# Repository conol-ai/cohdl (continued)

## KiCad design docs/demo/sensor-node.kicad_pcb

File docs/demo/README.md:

# MVP demo evidence

The acceptance test from the MVP Definition
(`docs/design/09-mvp-definition.md`): from a one-paragraph natural-language
spec — *"An ESP32-S3-based sensor node: USB-C power/data, one MEMS microphone,
one status LED, a 3.3V LDO regulator, standard decoupling"* — an LLM (no
fine-tuning, prompted only with the language reference) writes `.cohdl`
source; the compiler grades it; diagnostics are fed back verbatim; the loop
lands on a clean design that emits a real KiCad netlist + BOM.

Reproduce with `python3 harness/repair_loop.py` (see the harness README
header for backends).

## Runs (2026-07-13)

| Run | Model | Reference | Attempts | Caught & repaired |
|---|---|---|---|---|
| 1 | claude-opus-4-8 | full | 2 | E202 ×2 (unresolved name), D003 warning |
| 2 | claude-opus-4-8 | full | 1 | — clean first try |
| 3 | claude-opus-4-8 | full | 1 | — clean first try |
| 4 | claude-opus-4-8 | full, reworded spec | 1 | — clean first try |
| 5 | claude-opus-4-8 | lean (no design notes) | 1 | — clean first try |
| 6 | claude-opus-4-8 | lean, detailed spec | 2 | E202 (unresolved name) |
| 7 | claude-haiku-4-5 | lean | 1 | — clean first try |
| 8 | claude-opus-4-8 | lean, +custom tantalum device | 1 | — clean first try (wrote device + impl mapping + part correctly) |
| **9** | **claude-haiku-4-5** | **lean, +custom tantalum device** | **2** | **E701 — unresolved required pin, repaired** |

## The proof transcript

[`transcript-flagship-haiku-e701.md`](transcript-flagship-haiku-e701.md) is
the run the MVP's non-negotiable clause asks for. On attempt 1 the model left
the ESP32-S3's chip-enable pin unwired, and the **type checker** — not DRC —
caught it as a compile error naming the exact line:

```text
error[E701]: required pin `SensorNode::esp32.EN` is unresolved: add it to a `net` or explicitly mark it `nc`
 --> src/main.cohdl:20:5
   |
20 |     inst esp32: ESP32_S3_WROOM_1_N8
   |     ^^^^^^^^^^^^^^^^^^^^^^^^^^^^^^^
  :: std/soc.cohdl:13:9
   |
13 |         required EN: 3 [input]
   |         ---------------------- `EN` is declared `required` on device `ESP32_S3_WROOM_1` here
```

This is the exact mistake class (a forgotten wire) that v1 shipped silently
and that RFC-002 moved into the type system. The diagnostic was fed back
verbatim; attempt 2 wired EN through a 10k pull-up and landed clean —
[`sensor-node.net`](sensor-node.net) and
[`sensor-node-bom.csv`](sensor-node-bom.csv) are its emitted artifacts.

Two supplementary transcripts:

- [`transcript-opus-e202.md`](transcript-opus-e202.md) — a resolution-error
  catch + repair cycle (the model invented a v1-style bare net reference,
  which the MVP grammar deliberately dropped).
- [`transcript-opus-custom-device.md`](transcript-opus-custom-device.md) —
  the expressiveness half of the thesis: asked for a part the std library
  doesn't have, the model declared a polarized tantalum device, the explicit
  `impl TwoTerminal` pin mapping (`A: Anode, B: Cathode`), `impl Capacitor` +
  `impl Polarized`, and a part binding — all first try, all checked at the
  impl statements.

A note on difficulty: 6 of 9 runs were clean on the first attempt. The type
system's catches fire exactly when the model errs — with a complete language
reference in context, frontier models err rarely, which is the
AI-generatability half of the design working as intended (Constitution
priority #2). The failed attempts are what the compiler-as-oracle is for.

## KiCad checkpoint — executed

The import was driven through real KiCad (pcbnew 10.0.4, its own engine, via
`tools/kicad_checkpoint.py` — the same work File → Import Netlist performs):

- **All 14 footprints resolved from KiCad's official libraries**, every
  netlist pin matched a real footprint pad, designators verified unique.
- The resulting board is committed as
  [`sensor-node.kicad_pcb`](sensor-node.kicad_pcb) (open it directly in
  pcbnew — footprints placed, pad nets assigned, connectivity drawn), with a
  rendered [`sensor-node-board.pdf`](sensor-node-board.pdf) showing the
  components and net connectivity: USB-C → CC pulldowns, VBUS → LDO → 3.3V
  rail → decoupling bank + tantalum, ESP32 → I2S mic, EN pull-up, LED chain.

The checkpoint caught a real netlist-fidelity bug, exactly as intended: the
std USB-C device used combined pad names (`A1B12`, `S1`) that don't exist on
KiCad's official HRO footprint (separate `A1…B12` pads, shield `SH`). The std
device was corrected against the real footprint and everything regenerated.

To confirm by eye: open `sensor-node.kicad_pcb` in KiCad (or just the PDF),
and cross-check `sensor-node-bom.csv` — every line item carries a real MPN.

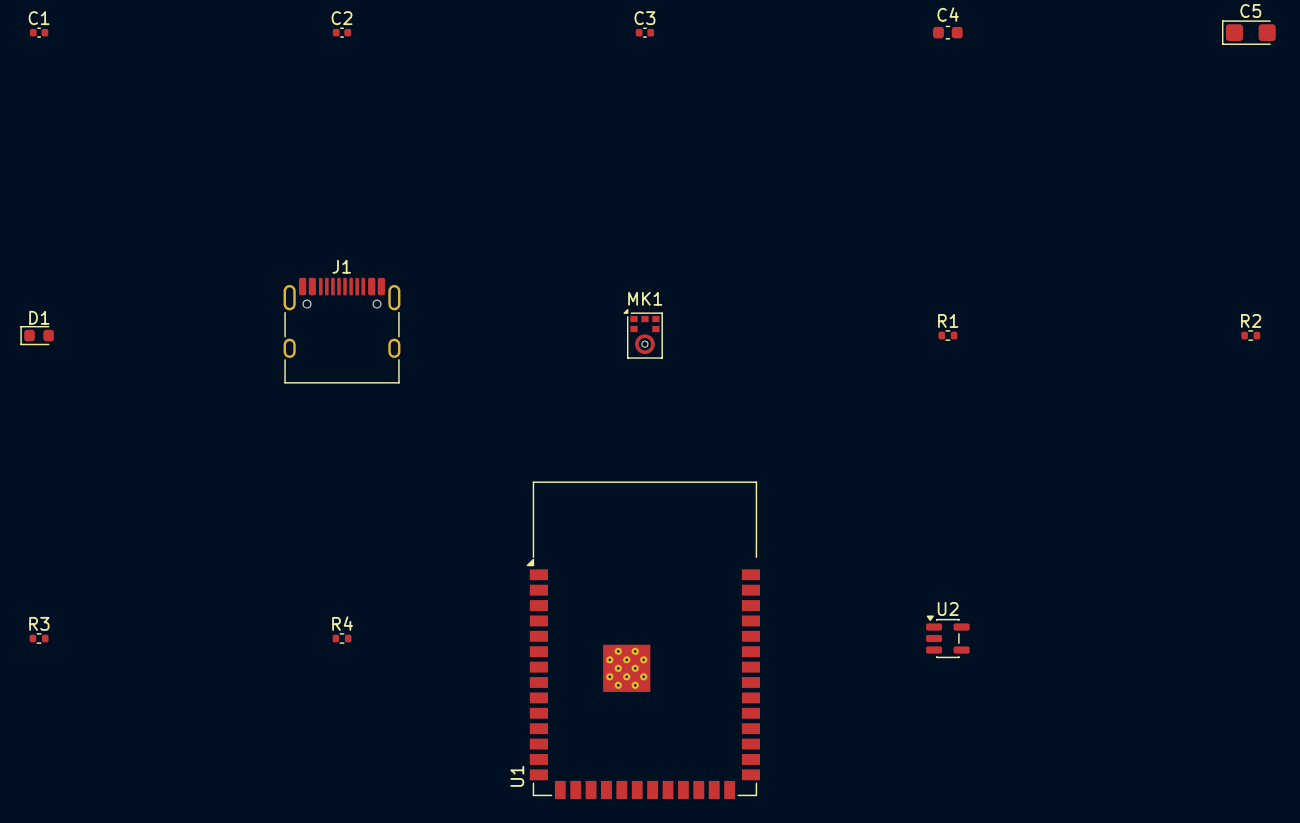
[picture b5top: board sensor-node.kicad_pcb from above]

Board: 2 copper layers, 14 parts (0 on the bottom side), 14 nets, no tracks yet.

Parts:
C1, C2, C3: 100nF; C_0402_1005Metric
C4: 10uF; C_0603_1608Metric
C5: 100uF; CP_EIA-3216-18_Kemet-A
D1: ChipLED; LED_0603_1608Metric
J1: USB_C_Receptacle_2_0; USB_C_Receptacle_HRO_TYPE-C-31-M-12
MK1: ICS43434; InvenSense_ICS-43434-6_3.5x2.65mm
R1: 1kohm; R_0402_1005Metric
R2, R3: 5.1kohm; R_0402_1005Metric
R4: 10kohm; R_0402_1005Metric
U1: ESP32_S3_WROOM_1; ESP32-S3-WROOM-1
U2: AP2112K_3V3; SOT-23-5

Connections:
CC1: J1.A5, R2.1
CC2: J1.B5, R3.1
DN: J1.A7, J1.B7, U1.13
DP: J1.A6, J1.B6, U1.14
EN: R4.2, U1.3
GND: C1.2, C2.2, C3.2, C4.2, C5.2, D1.1, J1.A1, J1.A12, J1.B1, J1.B12, J1.SH, MK1.6, R2.2, R3.2, U1.1, U1.40, U1.41, U2.2
LR: MK1.2, U1.15
SCK: MK1.3, U1.39
SD: MK1.4, U1.4
VBUS: J1.A4, J1.A9, J1.B4, J1.B9, U2.1
VDD: C1.1, C2.1, C3.1, C4.1, C5.1, MK1.5, R4.1, U1.2, U2.3, U2.5
WS: MK1.1, U1.38
__fn0_status_led::__net0: R1.1, U1.5
__fn0_status_led::__net1: D1.2, R1.2

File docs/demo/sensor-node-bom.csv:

RefDes,Value,MPN,Manufacturer,Qty
"U2","AP2112K_3V3","AP2112K-3.3TRG1","Diodes Inc",1
"C1,C2,C3","100nF","CL05B104KO5NNNC","Samsung",3
"C4","10uF","CL10A106KP8NNNC","Samsung",1
"U1","ESP32_S3_WROOM_1","ESP32-S3-WROOM-1-N8","Espressif",1
"MK1","ICS43434","ICS-43434","TDK InvenSense",1
"D1","ChipLED","LTST-C193KRKT-5A","Lite-On",1
"R4","10kohm","RC0402FR-0710KL","Yageo",1
"R1","1kohm","RC0402FR-071KL","Yageo",1
"R2,R3","5.1kohm","RC0402FR-075K1L","Yageo",2
"C5","100uF","T491A107K010AT","Kemet",1
"J1","USB_C_Receptacle_2_0","TYPE-C-31-M-12","HRO",1
